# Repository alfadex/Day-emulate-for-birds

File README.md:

# Day-light-emulate-for-birds

Operation of the project
https://github.com/alfadex/Day-emulate-for-birds/wiki

Ζero cross detection
https://alfadex.com/2014/02/dimming-230v-ac-with-arduino-2/

Bird timer Switch v.1
https://alfadex.com/2015/03/bird-timer-switch/

Bird timer Switch v.2
https://alfadex.com/2015/03/bird-timer-switch-v-2/

Code for this project refer to v.2

video
https://youtu.be/kFFZ-1XAeRA

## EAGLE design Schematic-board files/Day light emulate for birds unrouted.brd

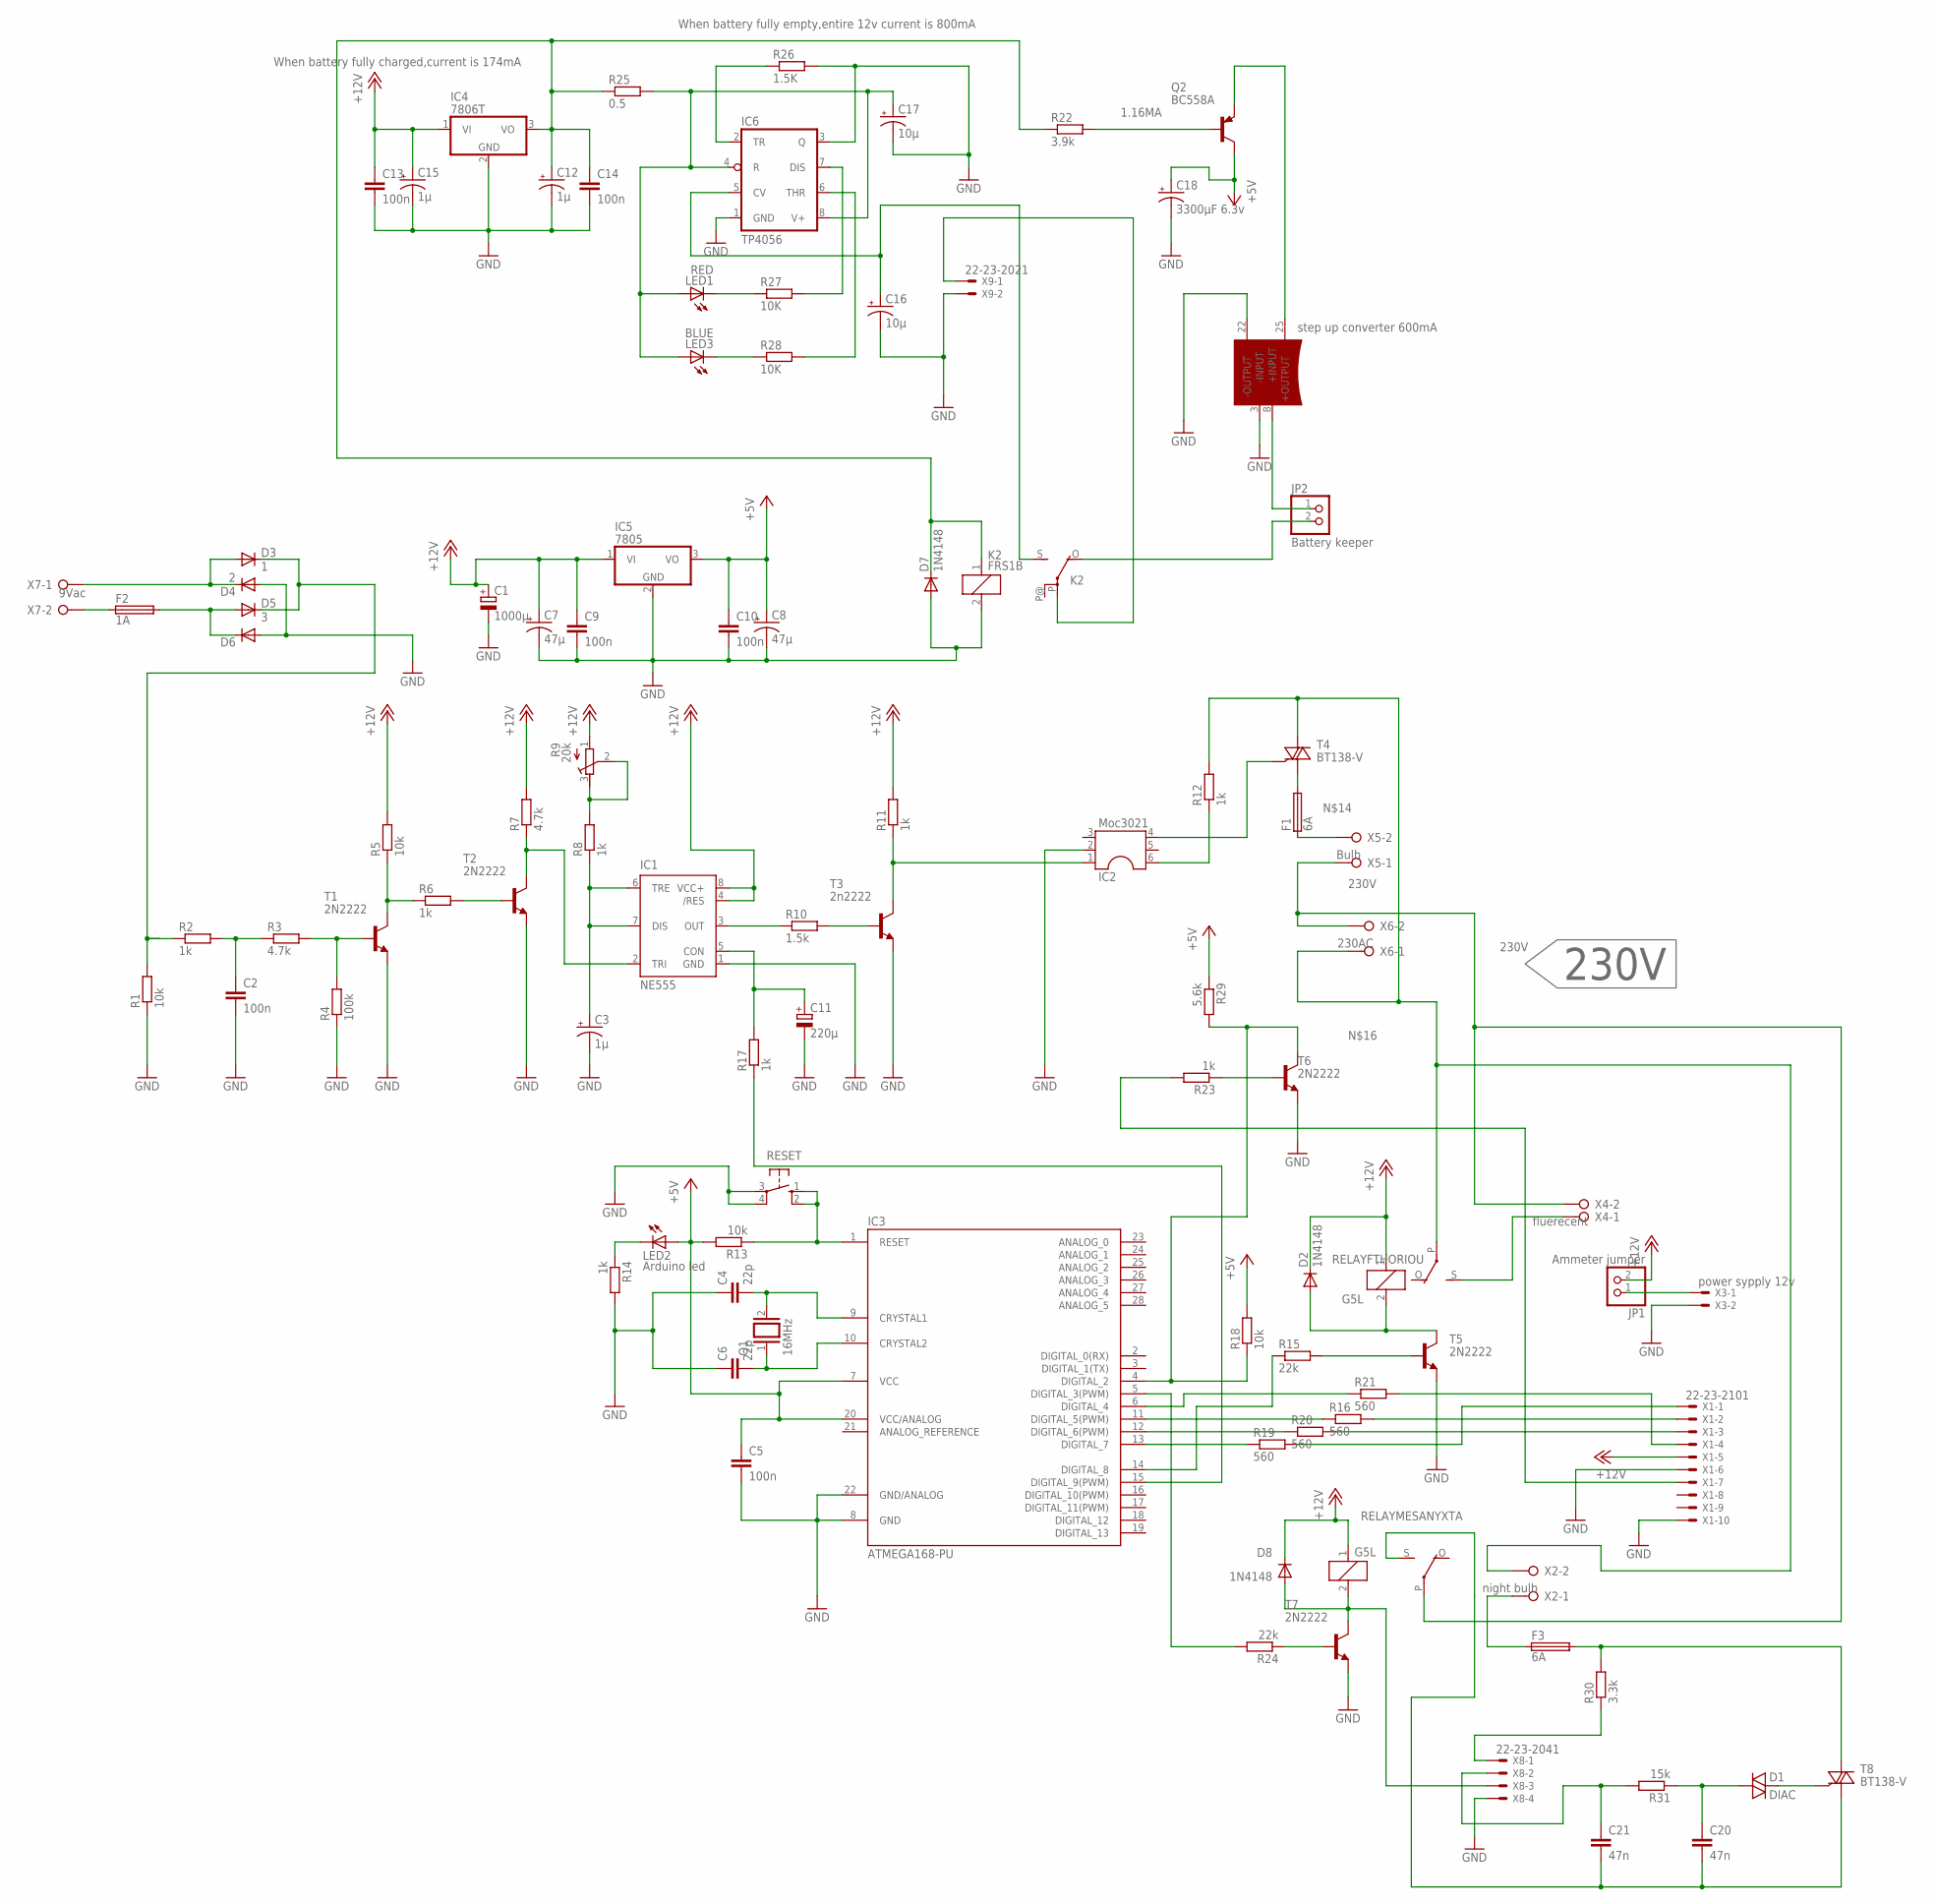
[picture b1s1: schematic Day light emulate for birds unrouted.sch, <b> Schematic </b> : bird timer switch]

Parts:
C1: 1000μ; E5-13
C2, C5, C9, C10, C13, C14: 100n; C025-030X050
C3, C12, C15: 1μ; E2-4
C4, C6: 22p; C025-030X050
C7, C8: 47μ; E2-4
C11: 220μ; E5-10,5
C16, C17: 10μ; E2-4
C18: 3300μF 6.3v; E5-6
C20, C21: 47n; C025-030X050
D1: DIAC; GT32
D2, D7, D8: 1N4148; DO35-10
D3: 1; DO41-10
D4: 2; DO41-10
D5: 3; DO41-10
D6: 1N4004; DO41-10
F1, F3: 6A; SHK20L
F2: 1A; SHK20L
IC1: NE555; DIL-08
IC2: Moc3021; DIL06
IC3: ATMEGA168-PU; DIL28-3
IC4: 7806T; TO220H
IC5: 7805; TO220V
IC6: TP4056; SO08
JP1: Ammeter jumper; 1X02
JP2: Battery keeper; 1X02
K2: FRS1B
LED1: RED; LED3MM
LED2: Arduino led; LED3MM
LED3: BLUE; LED3MM
Q1: 16MHz; QS
Q2: BC558A; TO92-EBC
R1, R5, R13, R18: 10k; 0207/10
R2, R6, R8, R11, R12, R14, R17, R23: 1k; 0207/10
R3, R7: 4.7k; 0207/10
R4: 100k; 0207/10
R9: 20k; RTRIM3339P
R10: 1.5k; 0207/10
R15, R24: 22k; 0207/10
R16, R19, R20, R21: 560; 0207/10
R22: 3.9k; 0207/10
R25: 0.5; 0207/10
R26: 1.5K; 0207/10
R27, R28: 10K; 0207/10
R29: 5.6k; 0207/10
R30: 3.3k; 0207/10
R31: 15k; 0207/10
RELAYFTHORIOU: G5L; G5LE
RELAYMESANYXTA: G5L; G5LE
RESET: 10-XX; B3F-10XX
STEPUP1: steup converter 600mA; STEPUP_CONVERTER_600MA
T1, T2, T5, T6, T7: 2N2222; TO18
T3: 2n2222; TO18
T4, T8: BT138-V; TO220BV
X1: 22-23-2101
X2: night bulb; W237-132
X3: power sypply 12v; 22-23-2021
X4: fluerecent; W237-132
X5: Bulb; W237-132
X6: 230AC; W237-132
X7: 9Vac; W237-132
X8: 22-23-2041
X9: 22-23-2021

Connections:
1.16MA: Q2.B, R22.2
230V: RELAYMESANYXTA.P, X4.2, X5.1, X6.2
+5V: C5.1, C8.+, C10.1, C18.+, IC3.7 (VCC), IC3.20 (VCC/ANALOG), IC5.3 (VO), LED2.A, Q2.C, R13.2, R18.2, R29.1
+12V: C1.+, C7.+, C9.1, C13.1, C15.+, D2.C, D8.C, IC1.4 (/RES), IC1.8 (VCC+), IC4.1 (VI), IC5.1 (VI), JP1.2, R5.2, R7.2, R9.1 (E), R11.2, RELAYFTHORIOU.1, RELAYMESANYXTA.1, X1.5
GND: C1.-, C2.2, C3.-, C4.1, C5.2, C6.1, C7.-, C8.-, C9.2, C10.2, C11.-, C12.-, C13.2, C14.2, C15.-, C16.-, C17.-, C18.-, D4.A, D6.A, D7.A, IC1.1 (GND), IC2.2, IC3.8 (GND), IC3.22 (GND/ANALOG), IC4.2 (GND), IC5.2 (GND), IC6.1 (GND), IC6.3 (Q), K2.2, R1.1, R4.1, R14.2, R26.2, RESET.3, RESET.4 (P1), STEPUP1.3 (-INPUT), STEPUP1.22 (-OUTPUT), T1.1 (E), T2.1 (E), T3.1 (E), T5.1 (E), T6.1 (E), T7.1 (E), X1.6, X1.10, X3.2, X8.4, X9.2
MORNING: R19.2, X1.1
unnamed: IC3.11 (DIGITAL_5(PWM)), R16.1
unnamed: C2.1, R2.2, R3.1
unnamed: R3.2, R4.2, T1.2 (B)
unnamed: R5.1, R6.1, T1.3 (C)
unnamed: R6.2, T2.2 (B)
unnamed: IC1.2 (TRI), R7.1, T2.3 (C)
unnamed: R8.2, R9.2 (S), R9.3 (A)
unnamed: IC1.3 (OUT), R10.1
unnamed: C3.+, IC1.6 (TRE), IC1.7 (DIS), R8.1
unnamed: R10.2, T3.2 (B)
unnamed: IC2.1, R11.1, T3.3 (C)
unnamed: IC2.6, R12.1
unnamed: IC2.4, T4.G
unnamed: F1.1A (1), X5.2
unnamed: JP2.1, STEPUP1.8 (+INPUT)
unnamed: R12.2, RELAYFTHORIOU.P, T4.T2 (A2), X2.2, X6.1
unnamed: F2.1A (1), X7.2
unnamed: IC3.1 (RESET), R13.1, RESET.1 (S), RESET.2 (S1)
unnamed: LED2.K (C), R14.1
unnamed: D1.2, T8.G
unnamed: C6.2, IC3.10 (CRYSTAL2), Q1.1
unnamed: C4.2, IC3.9 (CRYSTAL1), Q1.2
unnamed: IC3.14 (DIGITAL_8), R15.1
unnamed: R15.2, T5.2 (B)
unnamed: D2.A, RELAYFTHORIOU.2, T5.3 (C)
unnamed: IC3.13 (DIGITAL_7), R19.1
unnamed: C11.+, IC1.5 (CON), R17.2
unnamed: R16.2, X1.2
unnamed: IC3.15 (DIGITAL_9(PWM)), R17.1
unnamed: IC3.6 (DIGITAL_4), R21.1
unnamed: R21.2, X1.4
unnamed: RELAYFTHORIOU.S, X4.1
unnamed: IC3.12 (DIGITAL_6(PWM)), R20.1
unnamed: D3.A, D4.C, X7.1
unnamed: D5.A, D6.C, F2.2A (2)
unnamed: D3.C, D5.C, R1.2, R2.1
unnamed: R20.2, X1.3
unnamed: K2.P, X9.1
unnamed: JP2.2, K2.O
unnamed: C12.+, C14.1, D7.C, IC4.3 (VO), K2.1, R22.1, R25.1
unnamed: IC3.5 (DIGITAL_3(PWM)), R24.2
unnamed: R24.1, T7.2 (B)
unnamed: D8.A, RELAYMESANYXTA.2, T7.3 (C), X8.3
unnamed: C20.2, C21.2, RELAYMESANYXTA.S, T8.T1 (A1)
unnamed: Q2.E, STEPUP1.25 (+OUTPUT)
unnamed: C17.+, IC6.4 (R), IC6.8 (V+), LED1.A, LED3.A, R25.2
unnamed: IC6.7 (DIS), R27.2
unnamed: IC6.6 (THR), R28.2
unnamed: C16.+, IC6.5 (CV), K2.S
unnamed: LED1.K (C), R27.1
unnamed: IC6.2 (TR), R26.1
unnamed: LED3.K (C), R28.1
unnamed: JP1.1, X3.1
unnamed: R23.2, X1.7
unnamed: R23.1, T6.2 (B)
unnamed: IC3.4 (DIGITAL_2), R18.1, R29.2, T6.3 (C)
unnamed: C20.1, D1.1, R31.1
unnamed: C21.1, R31.2, X8.2
unnamed: R30.1, X8.1
unnamed: F3.1A (1), X2.1
unnamed: F3.2A (2), R30.2, T8.T2 (A2)
unnamed: F1.2A (2), T4.T1 (A1)

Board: 2 copper layers, 97 parts (3 on the bottom side), 68 nets, no tracks yet.
